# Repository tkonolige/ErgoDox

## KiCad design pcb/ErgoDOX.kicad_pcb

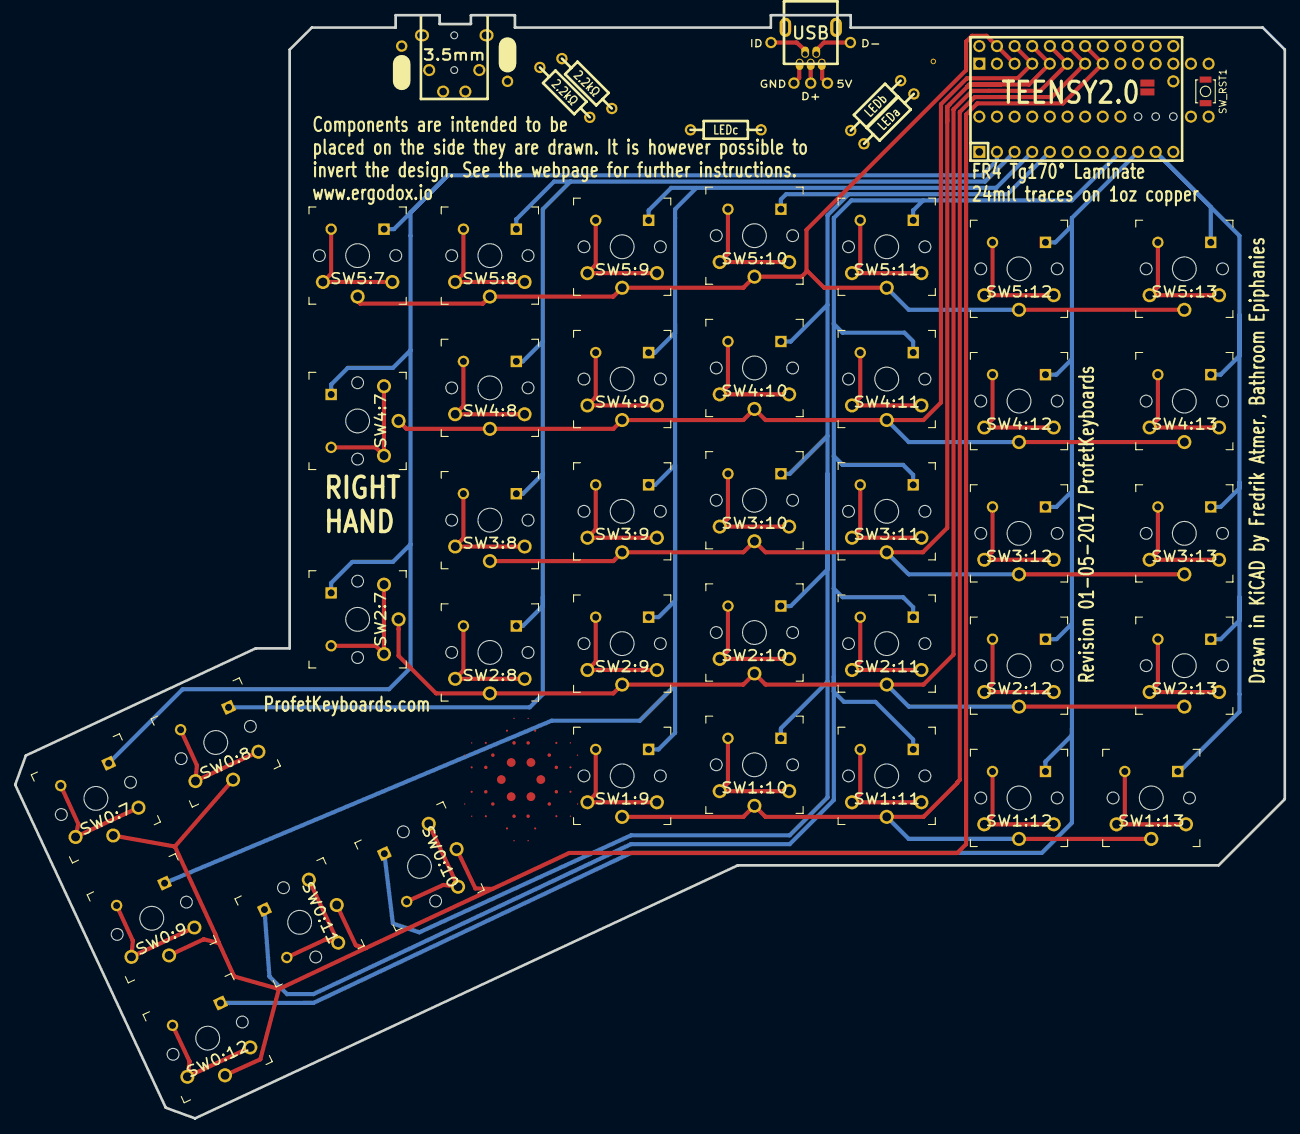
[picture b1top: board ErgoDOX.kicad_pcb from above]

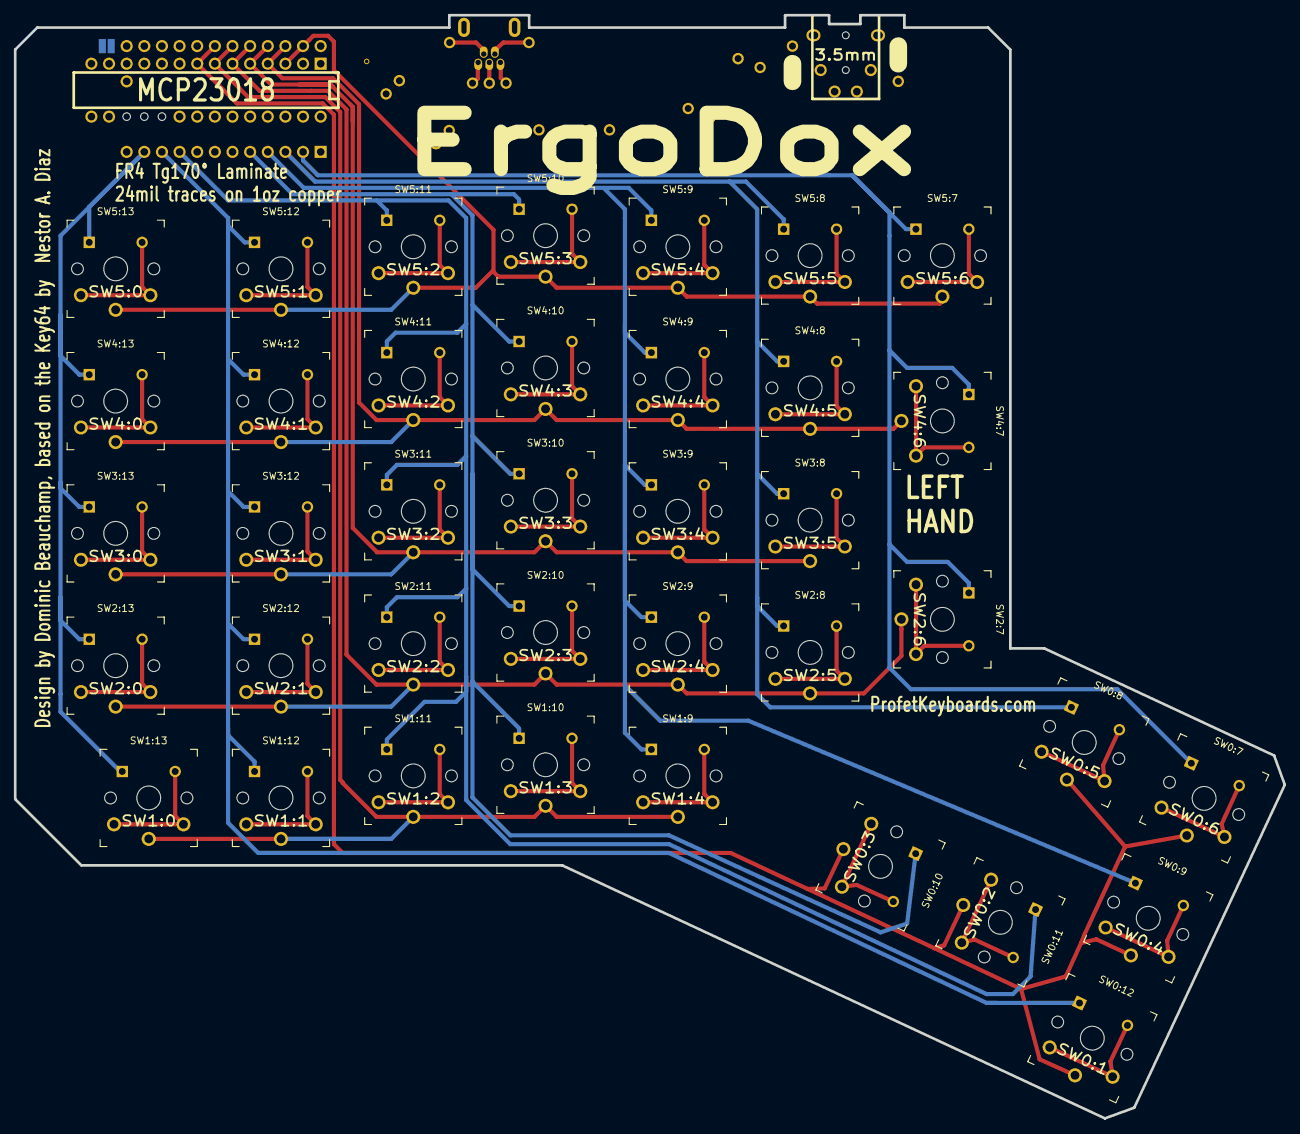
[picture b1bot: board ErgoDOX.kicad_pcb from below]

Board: 2 copper layers, 182.8 x 158.9 mm, 54 parts (3 on the bottom side), 61 nets.

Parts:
J1: USB; USBMINImod
J2: 3.5mm; 4pin35mmAudio
J3, J4: JMP; 100PITCH1X3
JP1, JP2: JUMPER; GAP
R1, R2: 2.2kΩ; RESISTOR
RA1: LEDa; RESISTOR
RB1: LEDb; RESISTOR
RC1: LEDc; RESISTOR
STAR_1: STAR_FRONT; STAR
STITCHING_VIA: STITCHING_VIA
SW0:7: SW0:6; SW_PG1350_reversible
SW0:8: SW0:5; SW_PG1350_reversible
SW0:9: SW0:4; SW_PG1350_reversible
SW0:10: SW0:3; SW_PG1350_reversible
SW0:11: SW0:2; SW_PG1350_reversible
SW0:12: SW0:1; SW_PG1350_reversible
SW1:9: SW1:4; SW_PG1350_reversible
SW1:10: SW1:3; SW_PG1350_reversible
SW1:11: SW1:2; SW_PG1350_reversible
SW1:12: SW1:1; SW_PG1350_reversible
SW1:13: SW1:0; SW_PG1350_reversible
SW2:7: SW2:6; SW_PG1350_reversible
SW2:8: SW2:5; SW_PG1350_reversible
SW2:9: SW2:4; SW_PG1350_reversible
SW2:10: SW2:3; SW_PG1350_reversible
SW2:11: SW2:2; SW_PG1350_reversible
SW2:12: SW2:1; SW_PG1350_reversible
SW2:13: SW2:0; SW_PG1350_reversible
SW3:8: SW3:5; SW_PG1350_reversible
SW3:9: SW3:4; SW_PG1350_reversible
SW3:10: SW3:3; SW_PG1350_reversible
SW3:11: SW3:2; SW_PG1350_reversible
SW3:12: SW3:1; SW_PG1350_reversible
SW3:13: SW3:0; SW_PG1350_reversible
SW4:7: SW4:6; SW_PG1350_reversible
SW4:8: SW4:5; SW_PG1350_reversible
SW4:9: SW4:4; SW_PG1350_reversible
SW4:10: SW4:3; SW_PG1350_reversible
SW4:11: SW4:2; SW_PG1350_reversible
SW4:12: SW4:1; SW_PG1350_reversible
SW4:13: SW4:0; SW_PG1350_reversible
SW5:7: SW5:6; SW_PG1350_reversible
SW5:8: SW5:5; SW_PG1350_reversible
SW5:9: SW5:4; SW_PG1350_reversible
SW5:10: SW5:3; SW_PG1350_reversible
SW5:11: SW5:2; SW_PG1350_reversible
SW5:12: SW5:1; SW_PG1350_reversible
SW5:13: SW5:0; SW_PG1350_reversible
SW_RST1: SWITCH_PUSH; SW_SPST_B3U-1000P
U1: TEENSY2.0; TEENSY_2.0_WITH_RESET
U2: MCP23018; DIP28_300

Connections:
/COL0: SW1:13.4, SW2:13.4, SW3:13.4, SW4:13.4, SW5:13.4, U1.11, U2.20
/COL1: SW0:12.4, SW1:12.4, SW2:12.4, SW3:12.4, SW4:12.4, SW5:12.4, U1.10, U2.21
/COL4: SW0:9.4, SW1:9.4, SW2:9.4, SW3:9.4, SW4:9.4, SW5:9.4, U1.4, U2.24
/COL5: SW0:8.4, SW2:8.4, SW3:8.4, SW4:8.4, SW5:8.4, U1.3, U2.25
/COL6: SW0:7.4, SW2:7.4, SW4:7.4, SW5:7.4, U1.2, U2.26
/COL10: SW0:10.4, SW1:10.4, SW2:10.4, SW3:10.4, SW4:10.4, SW5:10.4, U1.5, U2.23
/COL11: SW0:11.4, SW1:11.4, SW2:11.4, SW3:11.4, SW4:11.4, SW5:11.4, U1.9, U2.22
/LED_A: RA1.1, U1.21, U2.10
/LED_B: RB1.1, U1.22, U2.9
/LED_C: RC1.1, U1.6
/ROW0: SW0:7.1, SW0:8.1, SW0:9.1, SW0:10.1, SW0:11.1, SW0:12.1, U1.23, U2.8
/ROW1: SW1:9.1, SW1:10.1, SW1:11.1, SW1:12.1, SW1:13.1, U1.24, U2.7
/ROW2: SW2:7.1, SW2:8.1, SW2:9.1, SW2:10.1, SW2:11.1, SW2:12.1, SW2:13.1, U1.25, U2.6
/ROW3: SW3:8.1, SW3:9.1, SW3:10.1, SW3:11.1, SW3:12.1, SW3:13.1, U1.26, U2.5
/ROW4: SW4:7.1, SW4:8.1, SW4:9.1, SW4:10.1, SW4:11.1, SW4:12.1, SW4:13.1, U1.27, U2.4
/ROW5: SW5:7.1, SW5:8.1, SW5:9.1, SW5:10.1, SW5:11.1, SW5:12.1, SW5:13.1, U1.28, U2.3
/RST: SW_RST1.1, U1.16
/SCLM: J2.3, J2.5, R2.2, U1.7, U2.12
/SDAM: J2.2, J2.6, R1.2, U1.8, U2.13
GND: J1.6, J3.3, J4.3, JP2.1, STITCHING_VIA.GND, SW_RST1.2, U1.1, U1.18, U2.1, U2.15
unnamed: J1.1, J2.4, J4.2
unnamed: J1.5, J2.1, J3.2
unnamed: SW0:7.2, SW0:7.3
unnamed: SW0:8.2, SW0:8.3
unnamed: SW0:9.2, SW0:9.3
unnamed: SW0:10.2, SW0:10.3
unnamed: SW0:11.2, SW0:11.3
unnamed: SW0:12.2, SW0:12.3
unnamed: SW1:9.2, SW1:9.3
unnamed: SW1:10.2, SW1:10.3
unnamed: SW1:11.2, SW1:11.3
unnamed: SW1:12.2, SW1:12.3
unnamed: SW1:13.2, SW1:13.3
unnamed: SW2:7.2, SW2:7.3
unnamed: SW2:8.2, SW2:8.3
unnamed: SW2:9.2, SW2:9.3
unnamed: SW2:10.2, SW2:10.3
unnamed: SW2:11.2, SW2:11.3
unnamed: SW2:12.2, SW2:12.3
unnamed: SW2:13.2, SW2:13.3
unnamed: SW3:8.2, SW3:8.3
unnamed: SW3:9.2, SW3:9.3
unnamed: SW3:10.2, SW3:10.3
unnamed: SW3:11.2, SW3:11.3
unnamed: SW3:12.2, SW3:12.3
unnamed: SW3:13.2, SW3:13.3
unnamed: SW4:7.2, SW4:7.3
unnamed: SW4:8.2, SW4:8.3
unnamed: SW4:9.2, SW4:9.3
unnamed: SW4:10.2, SW4:10.3
unnamed: SW4:11.2, SW4:11.3
unnamed: SW4:12.2, SW4:12.3
unnamed: SW4:13.2, SW4:13.3
unnamed: SW5:7.2, SW5:7.3
unnamed: SW5:8.2, SW5:8.3
unnamed: SW5:9.2, SW5:9.3
unnamed: SW5:10.2, SW5:10.3
unnamed: SW5:11.2, SW5:11.3
unnamed: SW5:12.2, SW5:12.3
unnamed: SW5:13.2, SW5:13.3
VCC: J3.1, J4.1, JP1.1, R1.1, R2.1, U1.20, U1.29, U2.11, U2.16

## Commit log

2020-04-14 rename to pcb
2020-05-18 Added nrf-sdk
2021-01-19 starting routing
